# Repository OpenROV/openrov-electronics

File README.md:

<br>

<div align = center>

# OpenROV

***DIY Telerobotics*** for ***Underwater Exploration*** *&* ***Adventure*** *.*

<br>
<br>

[![Button Website]][Website]   
[![Button Forum]][Forum]   
[![Button BOM]][BOM]   
[![Button Hardware]][Hardware]

</div>

<br>
<br>

## Contents

This repository contains all files related<br>
to our **OpenROV DIY Kits**, these include <br>
`Schematics`, `Gerbers`, `Diagrams`, `..`

<br>
<br>

## Releases

<br>

-   **[`2.6`]**  |  **[`2.7`]**  |  **[`2.8`]**

    All-in-one power and control board that <br>
    has a Arduino based  `Atmega 2560`  board.
    
    Tons of I/O and designed to <br>
    fit the  `BeagleBone Black` .

    <br>

-   **[`2.5`]**

    All-in-one power & control board that has <br>
    a Arduino based  `Atmega 2560`  board.
    
    Tons of I/O and designed to fit both <br>
    `BeagleBone`  &  `BeagleBone Black` .

    <br>

-   **[`2.3`]**  |  **[`2.4`]**

    All-in-one power & control board <br>
    based around the  `Atmega 328` .

<br>

<!----------------------------------------------------------------------------->

[Hardware]: https://github.com/OpenROV/openrov-hardware
[Website]: http://openrov.com/
[Forum]: https://forum.openrov.com/
[BOM]: https://docs.google.com/spreadsheet/ccc?key=0Avf6fUwp9B3kdF9YQWxBTnZjZEVGZVQwY25EbnVyREE&usp=sharing

[`2.3`]: ./OpenROV%20BeagleBone%20Cape%20Rev%20A1%20v2.3%20v2.4
[`2.4`]: ./OpenROV%20BeagleBone%20Cape%20Rev%20A1%20v2.3%20v2.4
[`2.8`]: ./OpenROV%20Controller%202.8%20Final%20Data%20Pkg
[`2.7`]: ./OpenROV%20Controller%202.7%20Final%20Data%20Pkg
[`2.5`]: ./OpenROV%20Controller%202.5B
[`2.6`]: ./OpenROV%20Controller%202.6

<!---------------------------------[ Buttons ]--------------------------------->

[Button Hardware]: https://img.shields.io/badge/Hardware-81B441?style=for-the-badge&logoColor=white&logo=GodotEngine
[Button Website]: https://img.shields.io/badge/Website-1293D8?style=for-the-badge&logoColor=white&logo=GoogleChrome
[Button Forum]: https://img.shields.io/badge/Forum-782A90?style=for-the-badge&logoColor=white&logo=ElasticStack
[Button BOM]: https://img.shields.io/badge/Bill_Of_Material-E04E39?style=for-the-badge&logoColor=white&logo=Docs.rs

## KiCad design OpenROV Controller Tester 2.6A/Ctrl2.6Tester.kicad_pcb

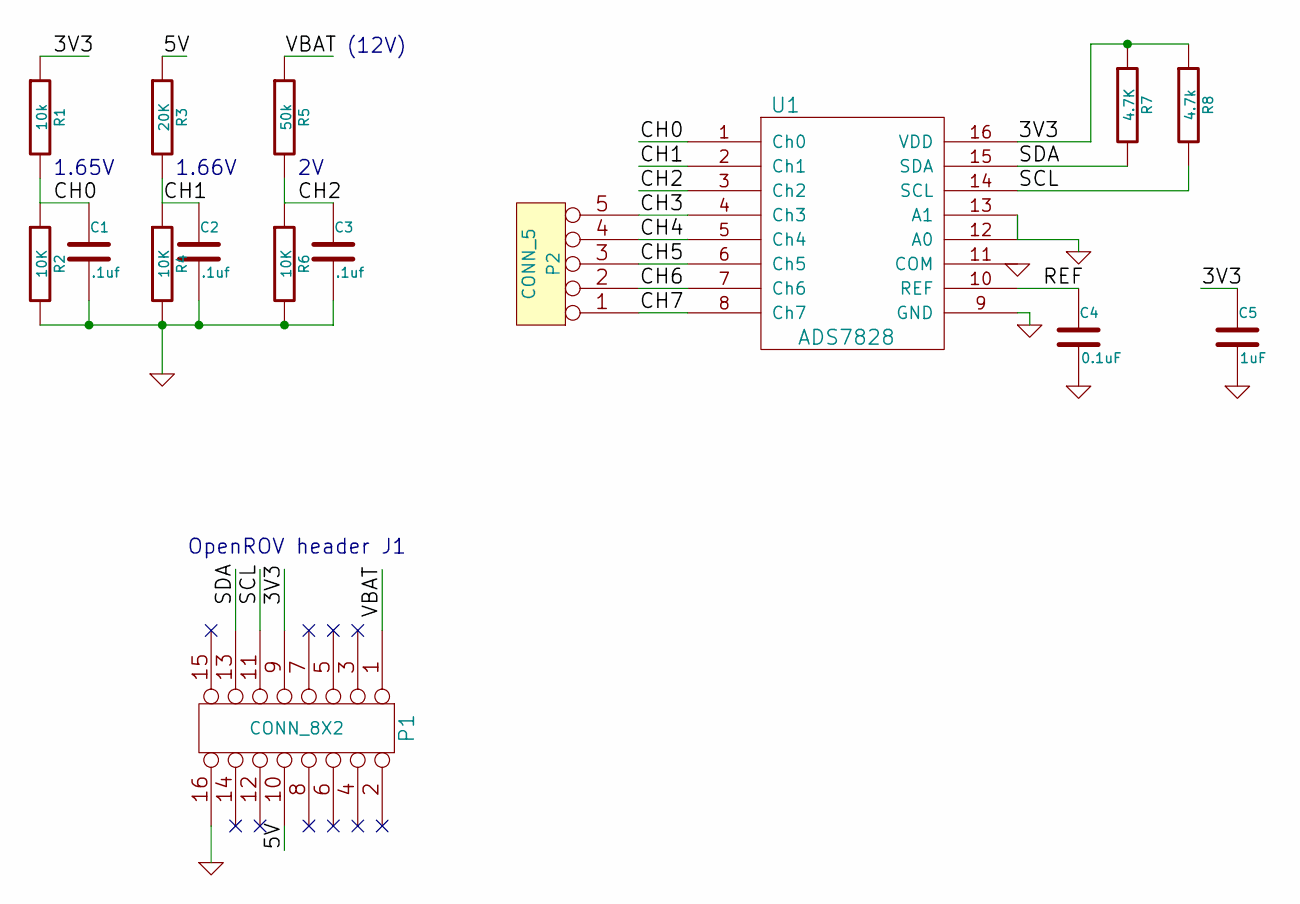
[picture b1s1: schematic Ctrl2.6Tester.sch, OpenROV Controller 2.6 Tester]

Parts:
C1, C2, C3: .1uf
C4: 0.1uF
C5: 1uF
P1: CONN_8X2
P2: CONN_5
R1: 10k
R2, R4, R6: 10K
R3: 20K
R5: 50k
R7: 4.7K
R8: 4.7k
U1: ADS7828

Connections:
/3V3: C5.1, P1.9, R1.1, R7.1, R8.1, U1.16 (VDD)
/5V: P1.10, R3.1
/CH0: C1.1, R1.2, R2.1, U1.1 (Ch0)
/CH1: C2.1, R3.2, R4.1, U1.2 (Ch1)
/CH2: C3.1, R5.2, R6.1, U1.3 (Ch2)
/CH3: P2.5, U1.4 (Ch3)
/CH4: P2.4, U1.5 (Ch4)
/CH5: P2.3, U1.6 (Ch5)
/CH6: P2.2, U1.7 (Ch6)
/CH7: P2.1, U1.8 (Ch7)
/REF: C4.1, U1.10 (REF)
/SCL: P1.11, R8.2, U1.14 (SCL)
/SDA: P1.13, R7.2, U1.15 (SDA)
/VBAT: P1.1, R5.1
GND: C1.2, C2.2, C3.2, C4.2, C5.2, P1.16, R2.2, R4.2, R6.2, U1.9 (GND), U1.11 (COM), U1.12 (A0), U1.13 (A1)

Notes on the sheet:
OpenROV header J1
1.65V
1.66V
(12V)

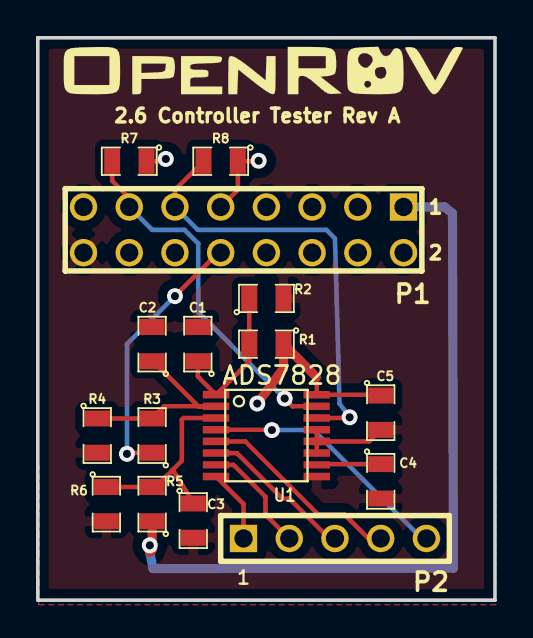
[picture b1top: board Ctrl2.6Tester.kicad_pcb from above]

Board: 2 copper layers, 25.4 x 31.2 mm, 15 parts (0 on the bottom side), 13 nets.

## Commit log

2012-06-04 Added Eagle sch file for OpenROV BeagleBone Cape
2012-06-09 updated with correct BB RX resistor placement
2012-06-09 changed voltage divider for arduino to work
2012-06-09 started on new cape board
2012-06-11 start of PCB layout based on the adafruit cape
2012-06-12 removed the extra beagle board header pins to make more room for arduino pins
2012-06-12 swapped out IC1 for official sparkfun atmega328 footprint
2012-06-12 swapped out the giant crystal footprint for a smaller standard one with the same hole spacing
2012-06-12 moved servo headers back over to the right side of the board
2012-06-12 added headers for +9V and +12V
2012-07-10 OpenROV Cape with features for first proto build
    Added
    *Arduino headers for shield
    *Lights for Power, UART Tx/Rx, and pin 13
    *Header for FTDI programmer
    *Power FETs for higher power PWM output
    *Header for tilt servo
2012-07-24 Added values and fixed errors
    Added/ corrected values to most components, corrected erroneous voltage
    divider configuration to TX-O, added resister between BBTX and RX-I,
    changed sheet labels
2012-07-26 Disambiguated several features
2012-12-03 Removing old schematics and adding the new cape, both PDF design schematics and gerber files
2012-12-03 Remove warning from readme
2013-01-04 Added wiring schematics, based on current cape design
    Wiring schematics, based on current cape design.
    Drawn in CADInt (www.cadint.se)
2013-03-18 Files for power distribution board
2013-05-21 Updated schematics to suit V2.4
2013-05-21 Revert "Files for power distribution board"
    This reverts commit c7d6c21a26aa24c1f079386188f363bcc68efe48.
2013-08-02 added Power Control Board 2.1 schematics, gerbers and PDFs
2013-09-27 added OpenROV Controller v2.5B files, gerbers, schematics. Reorganized folders
2013-09-27 Update README.md
    Updated info about folders, v2.5
2013-09-27 Update README.md
    formatting
2014-01-30 Added first version of Controller Tester that went out to manufacturing
2014-02-01 Added Controller 2.6 files and Topside Adapter Board 2.6 files
2014-02-20 added image of test jig setup and software needed to test control boards
2014-03-27 added IMU tester board pictures, software, and text file with info.
2014-12-17 Added 2.7 Controllerboard and the light board
2015-09-18 Added 2.8 Files
    2.8 Control Board Final Data Package, 2.8 Light Board Final Data Package
2015-09-23 Added IMU/Depth Module v2
    Data Package for IMU/Depth Module v2
2015-11-24 Added Light Board 2.8A Data Package
2015-11-24 Added External Light Cube Package
2015-12-09 BOM Rev 1 added
    Changed the LED to a more efficient one.
2016-03-16 Added 2.6A Data Package
2022-01-22 README Refactor
2022-08-11 Formatted README
